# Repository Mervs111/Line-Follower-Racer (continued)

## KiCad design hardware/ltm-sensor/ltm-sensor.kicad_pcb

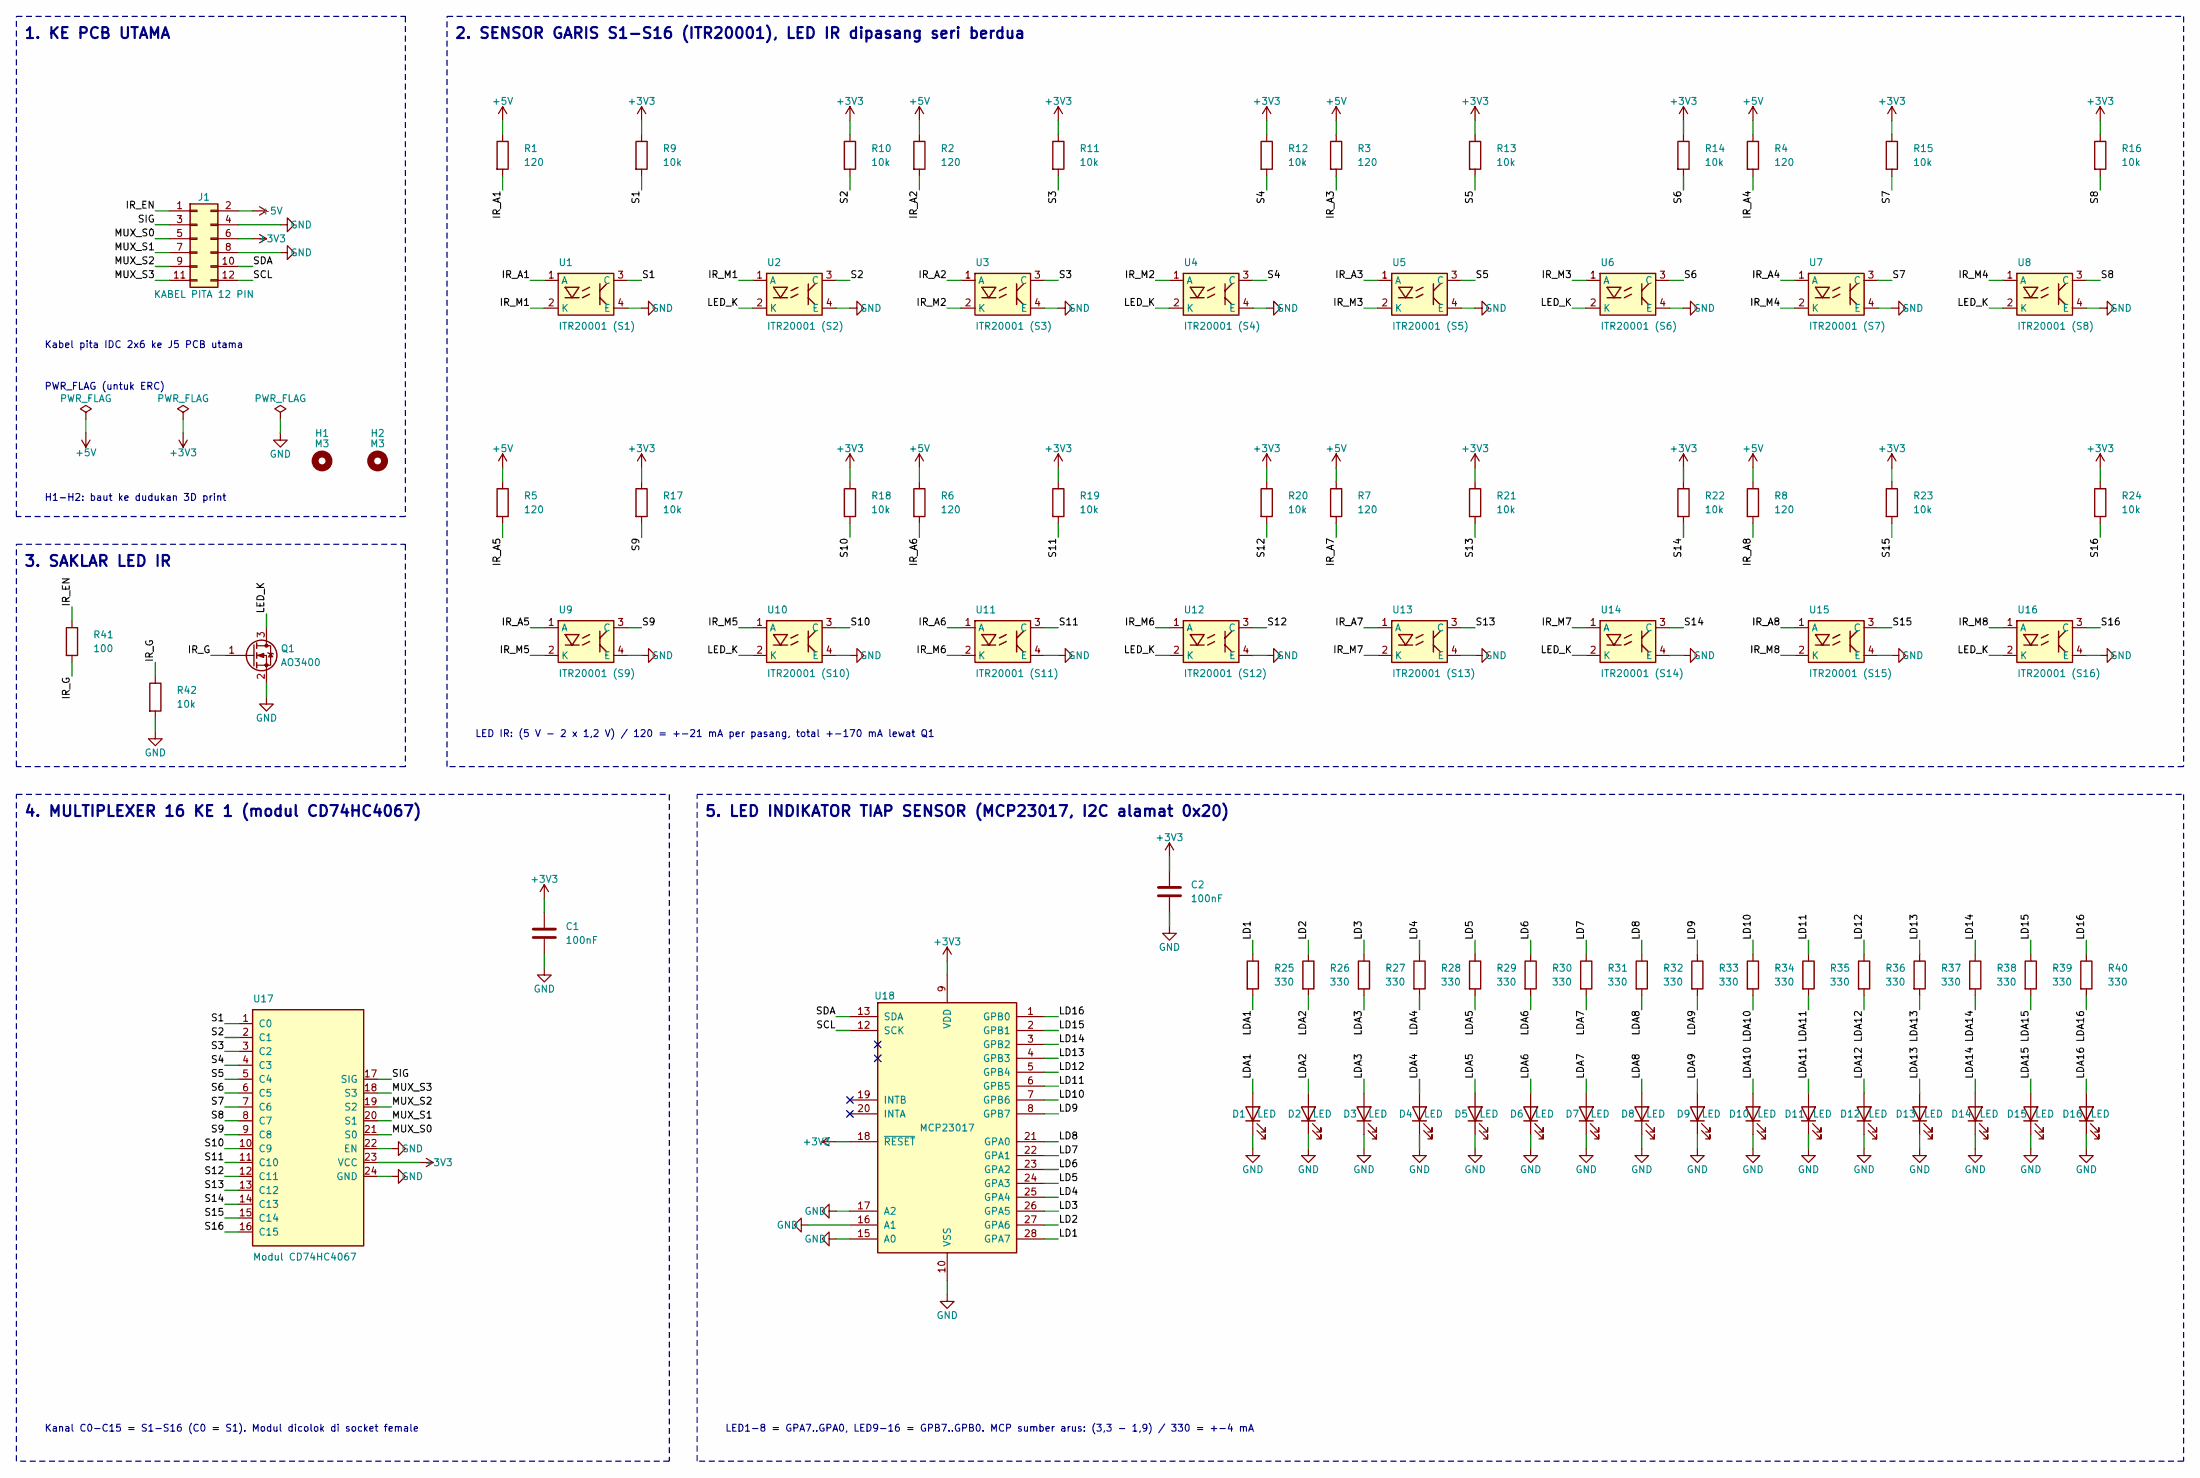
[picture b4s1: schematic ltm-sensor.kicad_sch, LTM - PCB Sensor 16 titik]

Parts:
C1, C2: 100nF; C_0805_2012Metric_Pad1.18x1.45mm_HandSolder
D1, D2, D3, D4, D5, D6, D7, D8, D9, D10, D11, D12, D13, D14, D15, D16: LED; LED_0805_2012Metric_Pad1.15x1.40mm_HandSolder
H1, H2: M3; MountingHole_3.2mm_M3
J1: KABEL PITA 12 PIN; IDC-Header_2x06_P2.54mm_Vertical
Q1: AO3400; SOT-23
R1, R2, R3, R4, R5, R6, R7, R8: 120; R_0805_2012Metric_Pad1.20x1.40mm_HandSolder
R9, R10, R11, R12, R13, R14, R15, R16, R17, R18, R19, R20, R21, R22, R23, R24, R42: 10k; R_0805_2012Metric_Pad1.20x1.40mm_HandSolder
R25, R26, R27, R28, R29, R30, R31, R32, R33, R34, R35, R36, R37, R38, R39, R40: 330; R_0805_2012Metric_Pad1.20x1.40mm_HandSolder
R41: 100; R_0805_2012Metric_Pad1.20x1.40mm_HandSolder
U1: ITR20001 (S1); ITR20001
U2: ITR20001 (S2); ITR20001
U3: ITR20001 (S3); ITR20001
U4: ITR20001 (S4); ITR20001
U5: ITR20001 (S5); ITR20001
U6: ITR20001 (S6); ITR20001
U7: ITR20001 (S7); ITR20001
U8: ITR20001 (S8); ITR20001
U9: ITR20001 (S9); ITR20001
U10: ITR20001 (S10); ITR20001
U11: ITR20001 (S11); ITR20001
U12: ITR20001 (S12); ITR20001
U13: ITR20001 (S13); ITR20001
U14: ITR20001 (S14); ITR20001
U15: ITR20001 (S15); ITR20001
U16: ITR20001 (S16); ITR20001
U17: Modul CD74HC4067; CD74HC4067_Module
U18: MCP23017; DIP-28_W7.62mm_Socket

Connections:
+3V3: C1.1, C2.1, J1.6, R9.1, R10.1, R11.1, R12.1, R13.1, R14.1, R15.1, R16.1, R17.1, R18.1, R19.1, R20.1, R21.1, R22.1, R23.1, R24.1, U17.23 (VCC), U18.9 (VDD), U18.18 (~RESET)
+5V: J1.2, R1.1, R2.1, R3.1, R4.1, R5.1, R6.1, R7.1, R8.1
/IR_A1: R1.2, U1.1 (A)
/IR_A2: R2.2, U3.1 (A)
/IR_A3: R3.2, U5.1 (A)
/IR_A4: R4.2, U7.1 (A)
/IR_A5: R5.2, U9.1 (A)
/IR_A6: R6.2, U11.1 (A)
/IR_A7: R7.2, U13.1 (A)
/IR_A8: R8.2, U15.1 (A)
/IR_EN: J1.1, R41.1
/IR_G: Q1.1 (G), R41.2, R42.1
/IR_M1: U1.2 (K), U2.1 (A)
/IR_M2: U3.2 (K), U4.1 (A)
/IR_M3: U5.2 (K), U6.1 (A)
/IR_M4: U7.2 (K), U8.1 (A)
/IR_M5: U9.2 (K), U10.1 (A)
/IR_M6: U11.2 (K), U12.1 (A)
/IR_M7: U13.2 (K), U14.1 (A)
/IR_M8: U15.2 (K), U16.1 (A)
/LD1: R25.1, U18.28 (GPA7)
/LD2: R26.1, U18.27 (GPA6)
/LD3: R27.1, U18.26 (GPA5)
/LD4: R28.1, U18.25 (GPA4)
/LD5: R29.1, U18.24 (GPA3)
/LD6: R30.1, U18.23 (GPA2)
/LD7: R31.1, U18.22 (GPA1)
/LD8: R32.1, U18.21 (GPA0)
/LD9: R33.1, U18.8 (GPB7)
/LD10: R34.1, U18.7 (GPB6)
/LD11: R35.1, U18.6 (GPB5)
/LD12: R36.1, U18.5 (GPB4)
/LD13: R37.1, U18.4 (GPB3)
/LD14: R38.1, U18.3 (GPB2)
/LD15: R39.1, U18.2 (GPB1)
/LD16: R40.1, U18.1 (GPB0)
/LDA1: D1.2 (A), R25.2
/LDA2: D2.2 (A), R26.2
/LDA3: D3.2 (A), R27.2
/LDA4: D4.2 (A), R28.2
/LDA5: D5.2 (A), R29.2
/LDA6: D6.2 (A), R30.2
/LDA7: D7.2 (A), R31.2
/LDA8: D8.2 (A), R32.2
/LDA9: D9.2 (A), R33.2
/LDA10: D10.2 (A), R34.2
/LDA11: D11.2 (A), R35.2
/LDA12: D12.2 (A), R36.2
/LDA13: D13.2 (A), R37.2
/LDA14: D14.2 (A), R38.2
/LDA15: D15.2 (A), R39.2
/LDA16: D16.2 (A), R40.2
/LED_K: Q1.3 (D), U2.2 (K), U4.2 (K), U6.2 (K), U8.2 (K), U10.2 (K), U12.2 (K), U14.2 (K), U16.2 (K)
/MUX_S0: J1.5, U17.21 (S0)
/MUX_S1: J1.7, U17.20 (S1)
/MUX_S2: J1.9, U17.19 (S2)
/MUX_S3: J1.11, U17.18 (S3)
/S1: R9.2, U1.3 (C), U17.1 (C0)
/S2: R10.2, U2.3 (C), U17.2 (C1)
/S3: R11.2, U3.3 (C), U17.3 (C2)
/S4: R12.2, U4.3 (C), U17.4 (C3)
/S5: R13.2, U5.3 (C), U17.5 (C4)
/S6: R14.2, U6.3 (C), U17.6 (C5)
/S7: R15.2, U7.3 (C), U17.7 (C6)
/S8: R16.2, U8.3 (C), U17.8 (C7)
/S9: R17.2, U9.3 (C), U17.9 (C8)
/S10: R18.2, U10.3 (C), U17.10 (C9)
/S11: R19.2, U11.3 (C), U17.11 (C10)
/S12: R20.2, U12.3 (C), U17.12 (C11)
/S13: R21.2, U13.3 (C), U17.13 (C12)
/S14: R22.2, U14.3 (C), U17.14 (C13)
/S15: R23.2, U15.3 (C), U17.15 (C14)
/S16: R24.2, U16.3 (C), U17.16 (C15)
/SCL: J1.12, U18.12 (SCK)
/SDA: J1.10, U18.13 (SDA)
/SIG: J1.3, U17.17 (SIG)
GND: C1.2, C2.2, D1.1 (K), D2.1 (K), D3.1 (K), D4.1 (K), D5.1 (K), D6.1 (K), D7.1 (K), D8.1 (K), D9.1 (K), D10.1 (K), D11.1 (K), D12.1 (K), D13.1 (K), D14.1 (K), D15.1 (K), D16.1 (K), J1.4, J1.8, Q1.2 (S), R42.2, U1.4 (E), U2.4 (E), U3.4 (E), U4.4 (E), U5.4 (E), U6.4 (E), U7.4 (E), U8.4 (E), U9.4 (E), U10.4 (E), U11.4 (E), U12.4 (E), U13.4 (E), U14.4 (E), U15.4 (E), U16.4 (E), U17.22 (EN), U17.24 (GND), U18.10 (VSS), U18.15 (A0), U18.16 (A1), U18.17 (A2)

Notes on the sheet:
1. KE PCB UTAMA
Kabel pita IDC 2x6 ke J5 PCB utama
PWR_FLAG (untuk ERC)
2. SENSOR GARIS S1-S16 (ITR20001), LED IR dipasang seri berdua
LED IR: (5 V - 2 x 1,2 V) / 120 = +-21 mA per pasang, total +-170 mA lewat Q1
3. SAKLAR LED IR
4. MULTIPLEXER 16 KE 1 (modul CD74HC4067)
Kanal C0-C15 = S1-S16 (C0 = S1). Modul dicolok di socket female
5. LED INDIKATOR TIAP SENSOR (MCP23017, I2C alamat 0x20)
LED1-8 = GPA7..GPA0, LED9-16 = GPB7..GPB0. MCP sumber arus: (3,3 - 1,9) / 330 = +-4 mA
H1-H2: baut ke dudukan 3D print

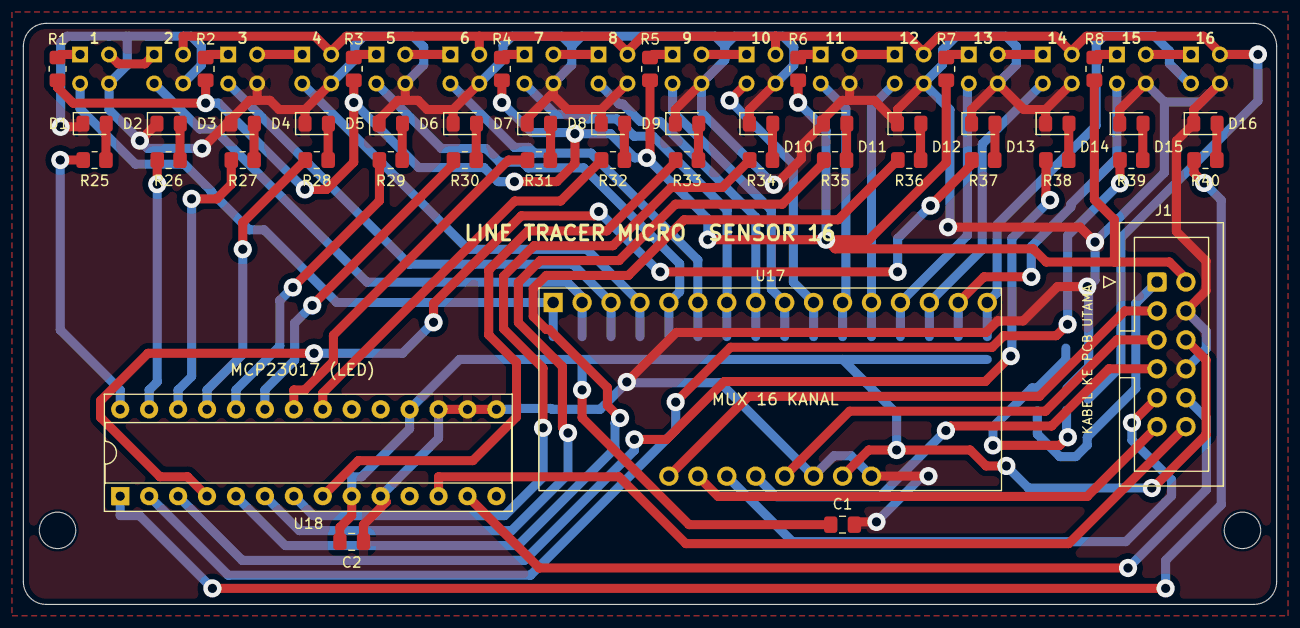
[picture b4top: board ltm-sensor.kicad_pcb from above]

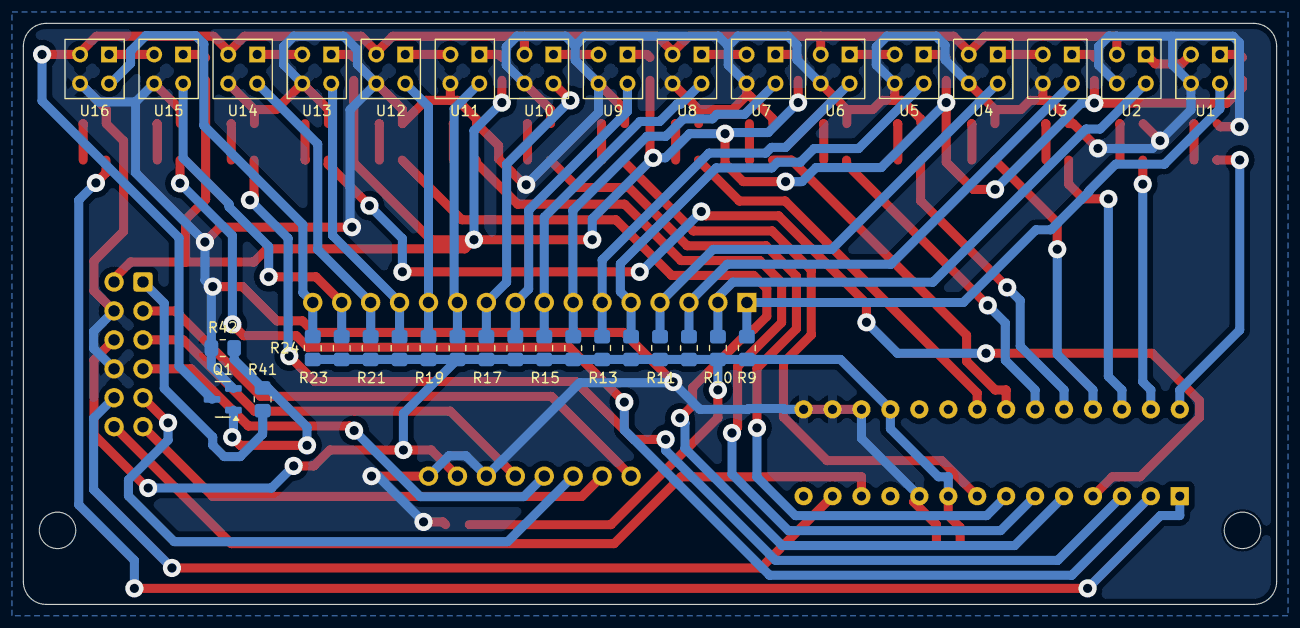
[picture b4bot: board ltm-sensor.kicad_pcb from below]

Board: 2 copper layers, 110.0 x 51.0 mm, 82 parts (35 on the bottom side), 77 nets.

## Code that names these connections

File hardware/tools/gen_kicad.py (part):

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            + "\n    ".join(props) + f"\n    {g}\n    (symbol \"{name}_1_1\"\n      {p}\n    )\n  )")


ESP32_LEFT = [("1", "EN", "input"), ("2", "GPIO36/VP", "input"), ("3", "GPIO39/VN", "input"),
              ("4", "GPIO34", "input"), ("5", "GPIO35", "input"), ("6", "GPIO32", "bidirectional"),
              ("7", "GPIO33", "bidirectional"), ("8", "GPIO25", "bidirectional"), ("9", "GPIO26", "bidirectional"),
              ("10", "GPIO27", "bidirectional"), ("11", "GPIO14", "bidirectional"), ("12", "GPIO12", "bidirectional"),
              ("13", "GPIO13", "bidirectional"), ("14", "GND", "power_in"), ("15", "VIN", "power_in")]
ESP32_RIGHT = [("16", "GPIO23", "bidirectional"), ("17", "GPIO22", "bidirectional"), ("18", "TX0/GPIO1", "bidirectional"),
               ("19", "RX0/GPIO3", "bidirectional"), ("20", "GPIO21", "bidirectional"), ("21", "GPIO19", "bidirectional"),
               ("22", "GPIO18", "bidirectional"), ("23", "GPIO5", "bidirectional"), ("24", "GPIO17/TX2", "bidirectional"),
               ("25", "GPIO16/RX2", "bidirectional"), ("26", "GPIO4", "bidirectional"), ("27", "GPIO2", "bidirectional"),
               ("28", "GPIO15", "bidirectional"), ("29", "GND", "power_in"), ("30", "3V3", "power_out")]
TB_LEFT = [("1", "PWMA", "input"), ("2", "AIN2", "input"), ("3", "AIN1", "input"), ("4", "STBY", "input"),
           ("5", "BIN1", "input"), ("6", "BIN2", "input"), ("7", "PWMB", "input"), ("8", "GND", "power_in")]
MUX_CTRL = [("SIG", "passive"), ("S3", "input"), ("S2", "input"), ("S1", "input"), ("S0", "input"), ("EN", "input"),
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
# pin kabel pita PCB utama (J5) <-> PCB sensor (J1)
# baris ganjil (dalam) = 6 sinyal, baris genap (luar) = daya + I2C; di kabel pita SIG diapit +5V dan GND
J_PINS = {"1": "IR_EN", "2": "+5V", "3": "SIG", "4": "GND", "5": "MUX_S0", "6": "+3V3", "7": "MUX_S1", "8": "GND",
          "9": "MUX_S2", "10": "SDA", "11": "MUX_S3", "12": "SCL"}
N_SENS = 16

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    s.part("Device:D_Schottky", "D1", "1N5819", 106.68, 66.04, FP["1N5819"], {"2": "+5V_BUCK", "1": "+5V"})
    s.part("Device:R", "R1", "100k", 30.48, 96.52, FP["R"], {"1": "VBAT", "2": "VBAT_SENSE"}, "right")
    s.part("Device:R", "R2", "33k", 48.26, 96.52, FP["R"], {"1": "VBAT_SENSE", "2": "GND"}, "right")
    s.text("Pembaca baterai: 8,4 V -> 2,08 V ke GPIO39", 20.32, 127.0)
    s.text("Kapasitor kecil tidak dipasang: modul TB6612,\nMP1584, dan ESP32 sudah punya kapasitor sendiri", 20.32, 119.38)
    s.text("PWR_FLAG (untuk ERC)", 99.06, 91.44)
    s.flag("GND", 101.6, 96.52)
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    esp_left = {"1": None, "2": "SIG", "3": "VBAT_SENSE", "4": "BTN_A", "5": "BTN_B", "6": "MUX_S3", "7": "MUX_S2",
                "8": "MUX_S1", "9": "MUX_S0", "10": "IR_EN", "11": "ENC_L_B", "12": "BUZ", "13": "ENC_L_A",
                "14": "GND", "15": "+5V"}
    # GPIO2 = STBY: LOW saat boot (pull-down TB6612) -> mode download aman & motor mati sampai firmware siap
    esp_right = {"16": "ENC_R_A", "17": "SCL", "18": None, "19": None, "20": "SDA", "21": "ENC_R_B", "22": "PWMA",
                 "23": "AIN1", "24": "AIN2", "25": "PWMB", "26": "BIN1", "27": "STBY", "28": "BIN2",
                 "29": "GND", "30": "+3V3"}
    s.part("ltm:ESP32_DevKit_30", "U1", "ESP32 DevKit 30P CH340", 212.09, 73.66, "ltm:ESP32_DevKit_30P_W25.4",
           {**esp_left, **esp_right})
    s.text("GPIO12 (BUZ) harus LOW saat boot: ada R4 10k di basis Q1", 165.1, 124.46)

    # ---- 3. DRIVER + MOTOR
    s.frame(271.78, 15.24, 408.94, 132.08, "3. DRIVER MOTOR + KONEKTOR MOTOR")
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    s.part("Switch:SW_Push", "SW3", "B (OK)", 50.8, 215.9, FP["BTN"], {"1": "BTN_B", "2": "GND"})
    s.part("Device:R", "R5", "10k", 81.28, 198.12, FP["R"], {"1": "+3V3", "2": "BTN_A"}, "right")
    s.part("Device:R", "R6", "10k", 81.28, 215.9, FP["R"], {"1": "+3V3", "2": "BTN_B"}, "right")
    s.text("GPIO34/35 tanpa pull-up internal: R5, R6", 20.32, 228.6)

    # ---- 5. BUZZER
    s.frame(116.84, 142.24, 215.9, 233.68, "5. BUZZER")
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    s.frame(223.52, 142.24, 312.42, 233.68, "6. KE PCB SENSOR (kabel pita IDC 12 pin)")
    s.part("Connector_Generic:Conn_02x06_Odd_Even", "J5", "KE PCB SENSOR", 264.16, 185.42, FP["IDC2x6"], J_PINS)
    s.text("Urutan pin sama persis dengan J1 PCB sensor", 228.6, 213.36)
    s.text("Mux: SIG GPIO36, S0-S3 GPIO32/33/2/15\nLED sensor: MCP23017 di bus I2C (0x20)", 228.6, 222.25)

    # ---- 7. LUBANG BAUT
    s.frame(320.04, 142.24, 408.94, 190.5, "7. LUBANG BAUT M3")
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
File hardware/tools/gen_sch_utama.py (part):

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digambar dengan kabel.

Rev B (03/11/2026, konsep v17): OLED dan tombol pindah ke board interface (hardware/board-interface/) lewat J6 1x6
(3V3, GND, SDA, SCL, BTN = tangga resistor 5 tombol di GPIO34, AUX = GPIO35 cadangan); R5 tetap jadi pull-up BTN supaya
GPIO34 tidak mengambang saat board interface dilepas. J2/J3 JST XH 6 pin, Q1 TO-92 Wide, C2 100 nF di VBAT_SENSE.
Catatan teks blok 2, 4, 5 sengaja tidak ditulis (dihapus user 29/10).

Jalankan dari folder repo: py hardware/tools/gen_sch_utama.py [--paksa]
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        (71.12, 71.12, "Set MP1584 ke 5,0 V dulu\nsebelum ESP32 dipasang"),
        (99.06, 52.07, "D1: cegah arus balik saat USB dicolok"),
        (17.78, 106.68, "C1 dekat pin VM TB6612"),
        (60.96, 106.68, "VBAT_SENSE ke GPIO39 (ADC1)"),
    ]),
    (144.78, 12.7, 406.4, 114.3, "2. DRIVER MOTOR + MOTOR  (wiring diagram blok 2)", []),
    (12.7, 119.38, 139.7, 248.92, "3. BOARD INTERFACE (OLED + 5 TOMBOL), BUZZER", [
        (63.5, 137.16, "J6: board interface ditumpuk di atas\n(OLED + tangga resistor 5 tombol)"),
        (17.78, 182.88, "R5 wajib: GPIO34 tanpa pull-up internal"),
        (86.36, 210.82, "R4 menjaga GPIO12 LOW\nsaat boot (syarat boot ESP32)"),
        (86.36, 222.25, "Q1 TO-92: cek urutan E-B-C"),
    ]),
    (144.78, 119.38, 276.86, 248.92, "4. ESP32 DEVKIT  (otak)", []),
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a, b = pin("R1", "2"), pin("R2", "1")
mid = (a[0], round((a[1] + b[1]) / 2 / 1.27) * 1.27)
wire(a, mid), wire(mid, b), JUNCS.append(mid)
wire(mid, (mid[0] + 5.08, mid[1])), label("VBAT_SENSE", (mid[0] + 5.08, mid[1]), 0)

# buzzer: BUZ - R3 - basis Q1, R4 basis ke GND, kolektor ke kaki - buzzer
r3b, qb, r4t = pin("R3", "2"), pin("Q1", "2"), pin("R4", "1")
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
